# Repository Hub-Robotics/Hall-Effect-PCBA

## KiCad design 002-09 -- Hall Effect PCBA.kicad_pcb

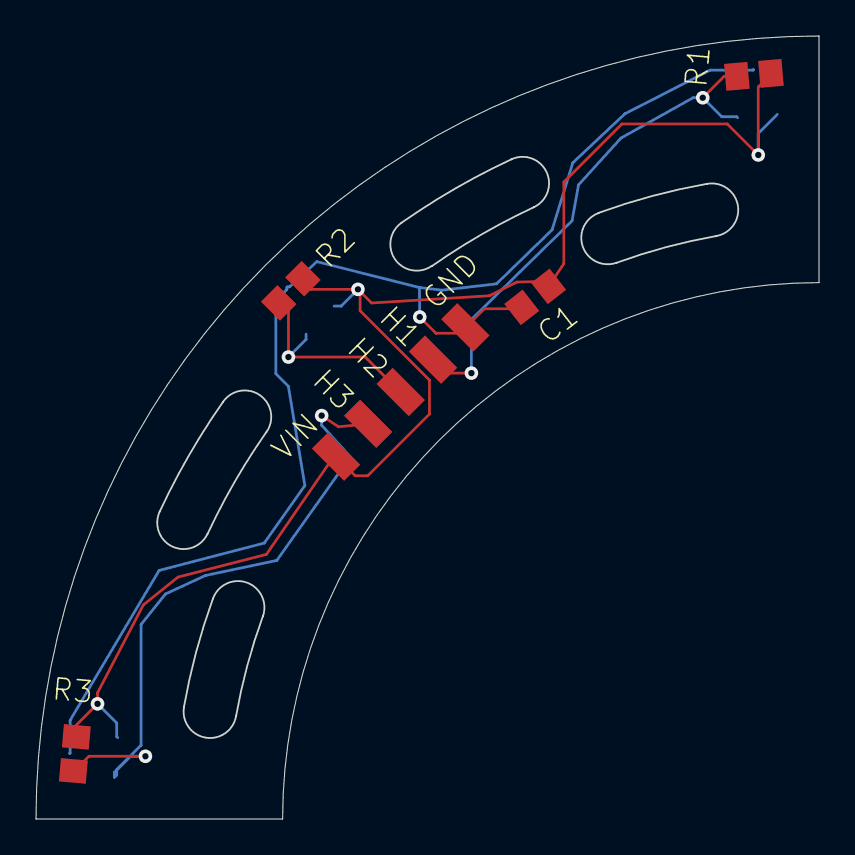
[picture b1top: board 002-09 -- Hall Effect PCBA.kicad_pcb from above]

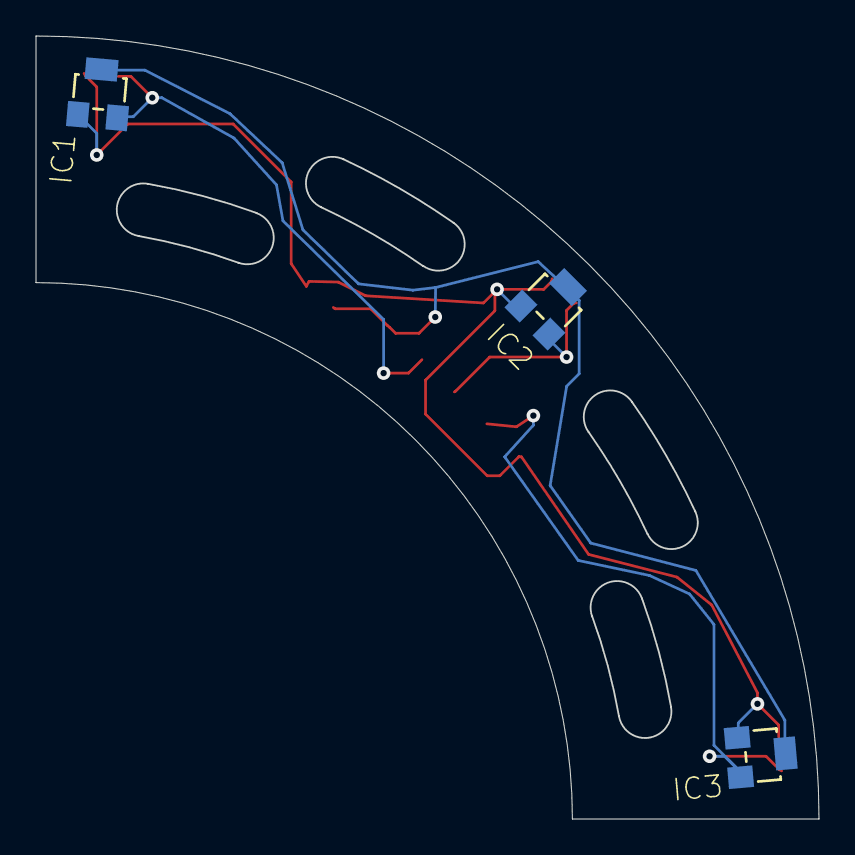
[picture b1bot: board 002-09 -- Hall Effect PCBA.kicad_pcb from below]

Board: 2 copper layers, 43.5 x 43.5 mm, 12 parts (3 on the bottom side), 5 nets.

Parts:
C1: 100nF; C0805
GND: SMD1,27-2,54
H1, H2, H3: SMD1,27-2,54
IC1, IC2, IC3: A1202LH; SOT23-W
R1, R2, R3: 10k; R0805
VIN: SMD1,27-2,54

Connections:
unnamed: C1.1, GND.1, IC1.3, IC2.3, IC3.3
unnamed: C1.2, IC1.1, IC2.1, IC3.1, R1.2, R2.2, R3.2, VIN.1
unnamed: H3.1, IC3.2, R3.1
unnamed: H2.1, IC2.2, R2.1
unnamed: H1.1, IC1.2, R1.1

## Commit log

2024-12-27 Adding files from local
2024-12-27 Adding files for v2.0 from local
2024-12-27 Added ECAD directory
